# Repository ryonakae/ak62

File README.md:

# AK62
A 60% Keyboard based on Apple M0116. Inspired by [Y62](https://geekhack.org/index.php?topic=76738.msg1923659)  
QMK Firmware is [here](https://github.com/ryonakae/qmk_firmware/tree/ryonakae/ak62/keyboards/ak62)

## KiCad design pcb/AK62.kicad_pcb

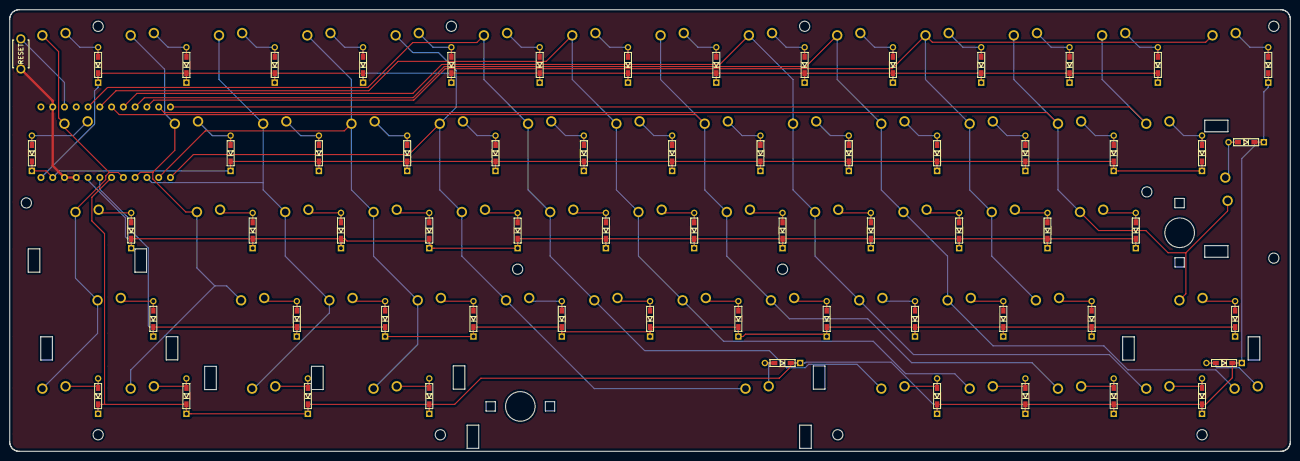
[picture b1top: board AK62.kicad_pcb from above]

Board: 2 copper layers, 276.2 x 95.3 mm, 139 parts (1 on the bottom side), 82 nets.

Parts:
D1, D2, D3, D4, D5, D6, D7, D8, D9, D10, D11, D12, D13, D14, D15, D16, D17, D18, D19, D20, D21, D22, D23, D24, D25, D26, D27, D28, D29, D30, D31, D32, D33, D34, D35, D36, D37, D38, D39, D40, D41, D42, D43, D44, D45, D46, D47, D48, D49, D50, D51, D52, D53, D54, D55, D56, D57, D58, D59, D60, D61, D62: D; D3_TH_SMD
HOLE1, HOLE2, HOLE3, HOLE4, HOLE5, HOLE6, HOLE7, HOLE8, HOLE9, HOLE10, HOLE11, HOLE12, HOLE13: MountingHole_2.2mm_M2
SW1, SW2, SW3, SW4, SW5, SW6, SW7, SW8, SW9, SW10, SW11, SW12, SW13, SW15, SW16, SW17, SW18, SW19, SW20, SW21, SW22, SW23, SW24, SW25, SW26, SW28, SW29, SW30, SW31, SW32, SW33, SW34, SW35, SW36, SW37, SW38, SW40, SW41, SW42, SW43, SW44, SW45, SW46, SW47, SW48, SW49, SW51, SW52, SW54, SW55, SW56, SW57, SW58, SW59, SW60, SW62: SW_PUSH; ALPS-1U
SW14, SW61: SW_PUSH; ALPS-1.5U
SW27, SW53: SW_PUSH; ALPS-1.75U
SW39, SW50: SW_PUSH; ALPS-2.25U
SW_RESET1: RESET_SWITCH; ResetSW
U1: ProMicro; ProMicro_v3

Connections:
GND: SW_RESET1.2, U1.3, U1.4, U1.23
unnamed: D1.2, SW1.2
unnamed: D2.2, SW2.2
unnamed: D3.2, SW3.2
unnamed: D4.2, SW4.2
unnamed: D5.2, SW5.2
unnamed: D6.2, SW6.2
unnamed: D7.2, SW7.2
unnamed: D8.2, SW8.2
unnamed: D9.2, SW9.2
unnamed: D10.2, SW10.2
unnamed: D11.2, SW11.2
unnamed: D12.2, SW12.2
unnamed: D13.2, SW13.2
unnamed: D14.2, SW14.2
unnamed: D15.2, SW15.2
unnamed: D16.2, SW16.2
unnamed: D17.2, SW17.2
unnamed: D18.2, SW18.2
unnamed: D19.2, SW19.2
unnamed: D20.2, SW20.2
unnamed: D21.2, SW21.2
unnamed: D22.2, SW22.2
unnamed: D23.2, SW23.2
unnamed: D24.2, SW24.2
unnamed: D25.2, SW25.2
unnamed: D26.2, SW26.2
unnamed: D27.2, SW27.2
unnamed: D28.2, SW28.2
unnamed: D29.2, SW29.2
unnamed: D30.2, SW30.2
unnamed: D31.2, SW31.2
unnamed: D32.2, SW32.2
unnamed: D33.2, SW33.2
unnamed: D34.2, SW34.2
unnamed: D35.2, SW35.2
unnamed: D36.2, SW36.2
unnamed: D37.2, SW37.2
unnamed: D38.2, SW38.2
unnamed: D39.2, SW39.2
unnamed: D40.2, SW40.2
unnamed: D41.2, SW41.2
unnamed: D42.2, SW42.2
unnamed: D43.2, SW43.2
unnamed: D44.2, SW44.2
unnamed: D45.2, SW45.2
unnamed: D46.2, SW46.2
unnamed: D47.2, SW47.2
unnamed: D48.2, SW48.2
unnamed: D49.2, SW49.2
unnamed: D50.2, SW50.2
unnamed: D51.2, SW51.2
unnamed: D52.2, SW52.2
unnamed: D53.2, SW53.2
unnamed: D54.2, SW54.2
unnamed: D55.2, SW55.2
unnamed: D56.2, SW56.2
unnamed: D57.2, SW57.2
unnamed: D58.2, SW58.2
unnamed: D59.2, SW59.2
unnamed: D60.2, SW60.2
unnamed: D61.2, SW61.2
unnamed: D62.2, SW62.2
col0: SW1.1, SW14.1, SW27.1, SW39.1, SW51.1, U1.8
col1: SW2.1, SW15.1, SW28.1, SW40.1, SW52.1, U1.9
col2: SW3.1, SW16.1, SW29.1, SW41.1, SW53.1, U1.10
col3: SW4.1, SW17.1, SW30.1, SW42.1, SW54.1, U1.11
col4: SW5.1, SW18.1, SW31.1, SW43.1, SW55.1, U1.12
col5: SW6.1, SW19.1, SW32.1, SW44.1, SW56.1, U1.20
col6: SW7.1, SW20.1, SW33.1, SW45.1, SW57.1, U1.19
col7: SW8.1, SW21.1, SW34.1, SW46.1, SW58.1, U1.18
col8: SW9.1, SW22.1, SW35.1, SW47.1, SW59.1, U1.17
col9: SW10.1, SW23.1, SW36.1, SW48.1, SW60.1, U1.16
col10: SW11.1, SW24.1, SW37.1, SW49.1, SW61.1, U1.15
col11: SW12.1, SW25.1, SW38.1, SW50.1, SW62.1, U1.14
col12: SW13.1, SW26.1, U1.13
reset: SW_RESET1.1, U1.22
row0: D1.1, D2.1, D3.1, D4.1, D5.1, D6.1, D7.1, D8.1, D9.1, D10.1, D11.1, D12.1, D13.1, U1.1
row1: D14.1, D15.1, D16.1, D17.1, D18.1, D19.1, D20.1, D21.1, D22.1, D23.1, D24.1, D25.1, D26.1, U1.2
row2: D27.1, D28.1, D29.1, D30.1, D31.1, D32.1, D33.1, D34.1, D35.1, D36.1, D37.1, D38.1, U1.5
row3: D39.1, D40.1, D41.1, D42.1, D43.1, D44.1, D45.1, D46.1, D47.1, D48.1, D49.1, D50.1, U1.6
row4: D51.1, D52.1, D53.1, D54.1, D55.1, D56.1, D57.1, D58.1, D59.1, D60.1, D61.1, D62.1, U1.7

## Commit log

2019-07-17 add files
2019-07-17 add license
2019-07-23 pcb top plate wip
2019-07-27 update plate
